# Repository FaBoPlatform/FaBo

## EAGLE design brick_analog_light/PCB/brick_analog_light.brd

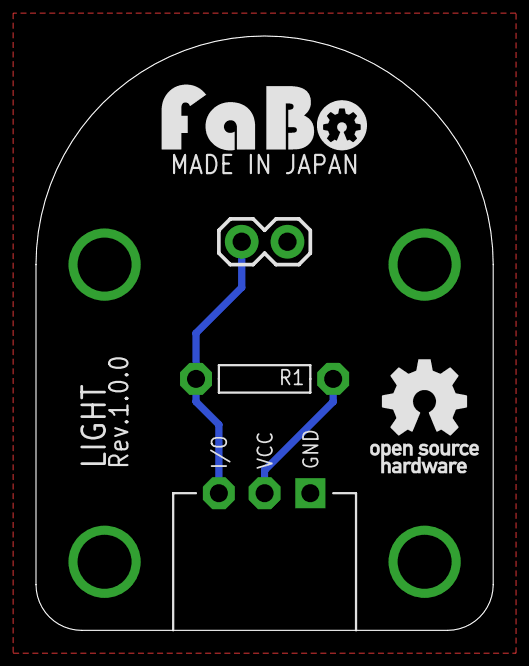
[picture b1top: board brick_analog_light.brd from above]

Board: 2 copper layers, 25.4 x 33.0 mm, 5 parts (0 on the bottom side), 3 nets.

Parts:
J1: FABO_BRICK_3PIN
R1: 10k; RES-AXL-REGULAR
U1: 1X02
U$2: LOGO_OSHW_T_M
U$3: LOGO_FABO_M

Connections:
GND: J1.GND, U1.2
unnamed: J1.VCC, R1.P$1
unnamed: J1.IN/OUT, R1.P$2, U1.1

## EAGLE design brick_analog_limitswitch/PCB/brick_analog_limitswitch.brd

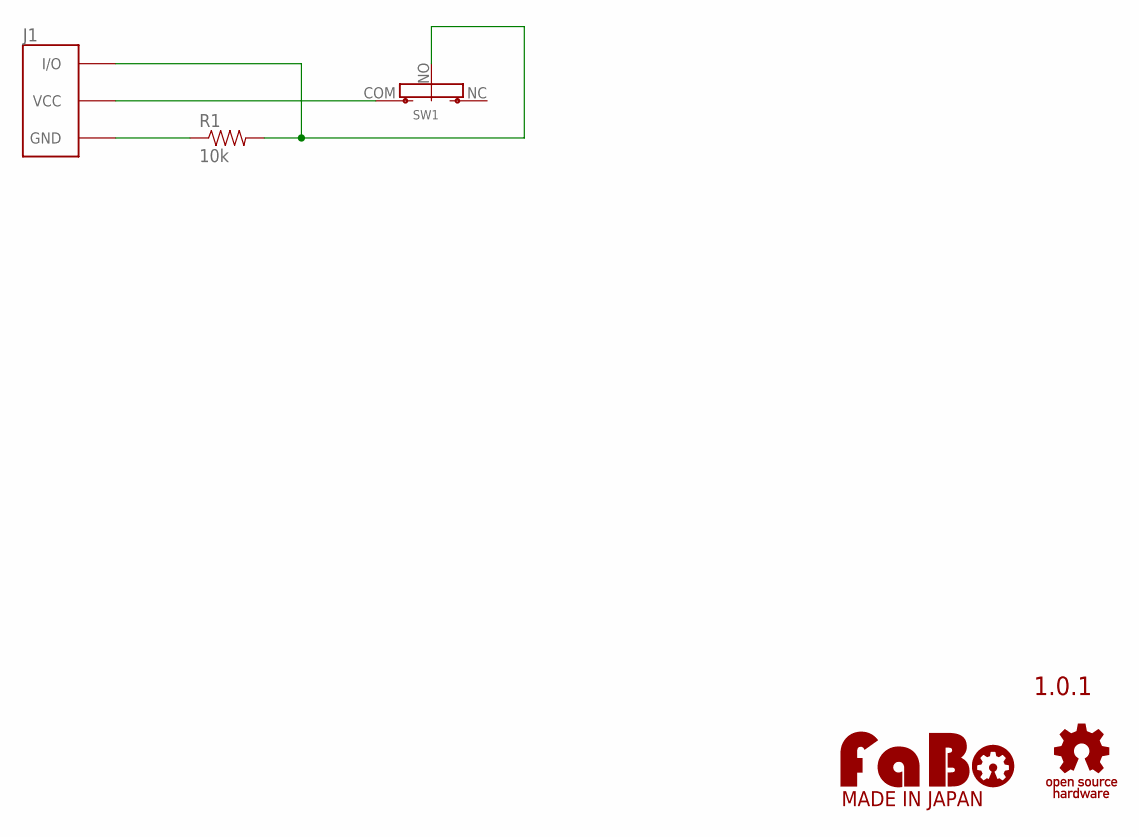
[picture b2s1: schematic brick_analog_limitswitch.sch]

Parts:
J1: FABO_BRICK_3PIN
R1: 10k; RES-AXL-REGULAR
SW1: LIMIT-SWITCH
U$2: LOGO_OSHW-T_M; LOGO_OSHW_T_M
U$4: LOGO_FABO-M; LOGO_FABO_M

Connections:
GND: J1.GND, R1.P$1 (1)
unnamed: J1.VCC, SW1.COM (VCC)
unnamed: J1.IN/OUT (I/O), R1.P$2 (2), SW1.NO

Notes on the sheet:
1.0.1

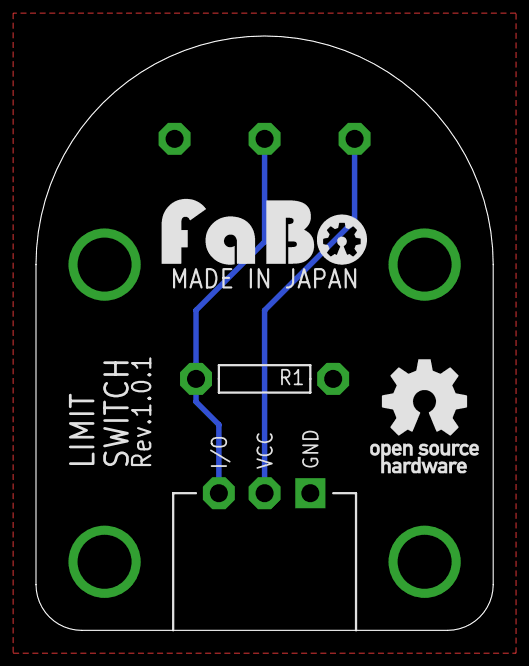
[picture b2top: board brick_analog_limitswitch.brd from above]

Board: 2 copper layers, 25.4 x 33.0 mm, 5 parts (0 on the bottom side), 3 nets.

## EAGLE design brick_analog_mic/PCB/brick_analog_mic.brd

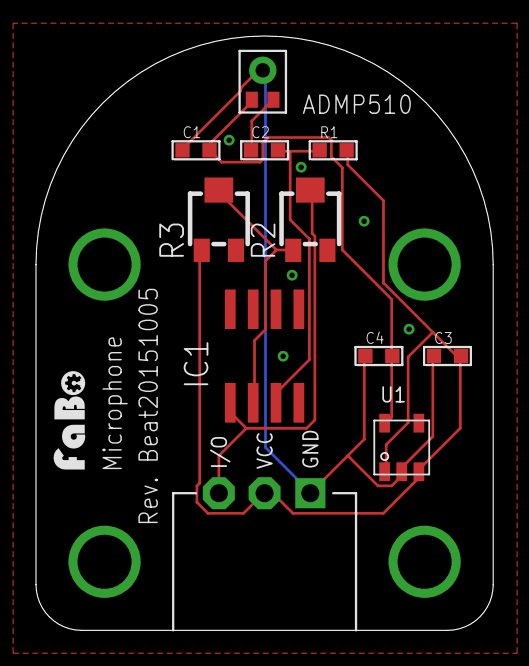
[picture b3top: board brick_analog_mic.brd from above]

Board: 2 copper layers, 25.4 x 33.0 mm, 12 parts (0 on the bottom side), 7 nets.

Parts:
C1: 0.1uF; 0603
C2, C3, C4: 1uf; 0603
IC1: ADA4075; SO8
J1: FABO_BRICK_3PIN
R1: 10k; 0603
R2, R3: RTRIM3202
U1: SOT_23_5
U$1: ANALOGDEVICES-ADMP510
U$2: LOGO_FABO_S

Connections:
3V3: C1.2, C4.2, U1.5, U$1.1
5V: C3.2, J1.VCC, R1.2, R3.1, U1.1, U1.3
GND: C1.1, C3.1, C4.1, J1.GND, U1.2, U$1.3
unnamed: C2.1, U$1.2
unnamed: C2.2, IC1.3, R1.1
unnamed: IC1.1, J1.IN/OUT, R2.2
unnamed: IC1.2, R2.1, R3.2

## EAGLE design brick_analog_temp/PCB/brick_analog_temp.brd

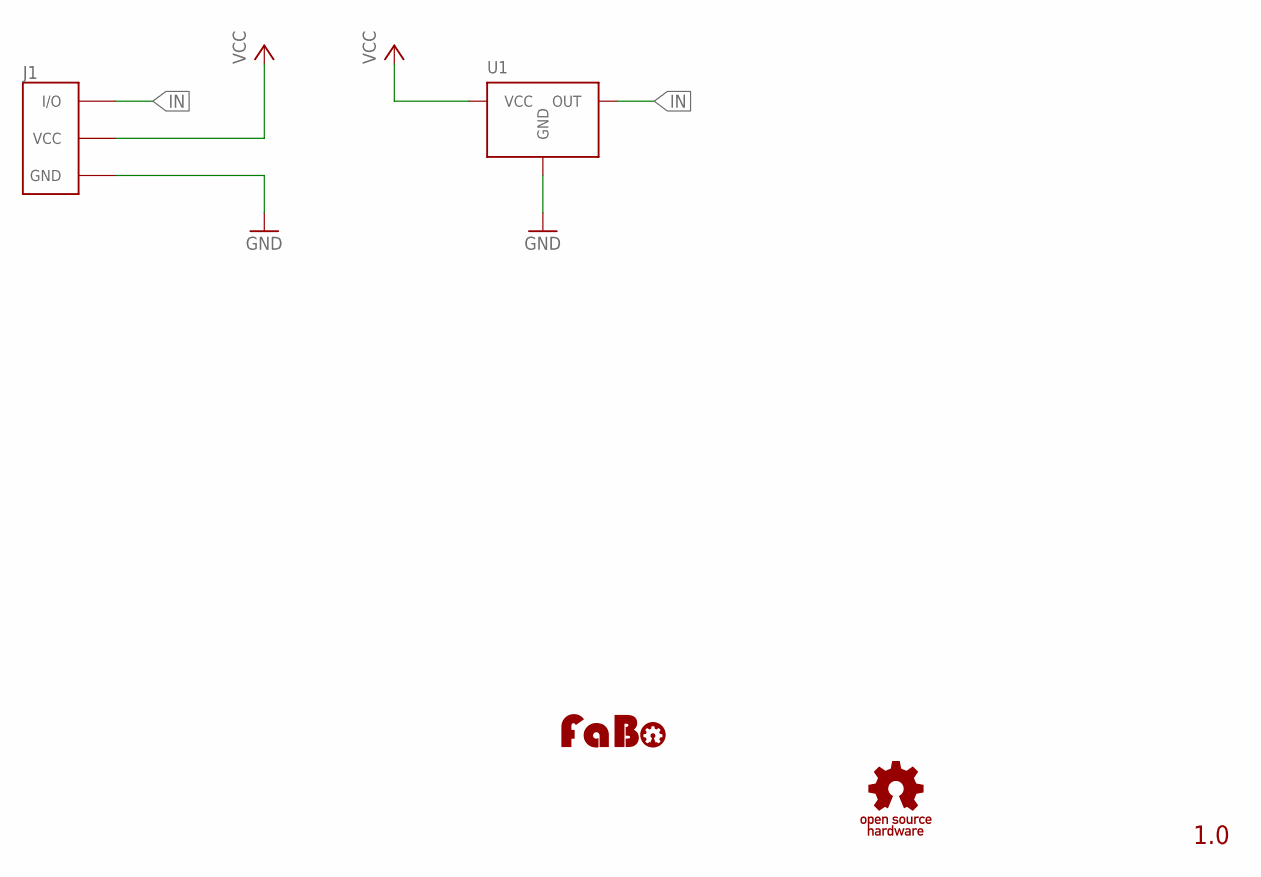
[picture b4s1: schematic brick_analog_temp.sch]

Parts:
J1: BRICK_3PIN_NORMAL; BRICK_3PIN
U1: SENSOR-LM60-TO92; SENSOR-LM60-TO-92
U$2: LOGO_OSHW_T-M; LOGO_OSHW_T_M
U$3: LOGO_FABO-M; LOGO_FABO_M

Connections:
GND: J1.GND, U1.GND
IN: J1.IN/OUT (I/O), U1.OUT
VCC: J1.VCC, U1.VCC

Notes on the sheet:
1.0

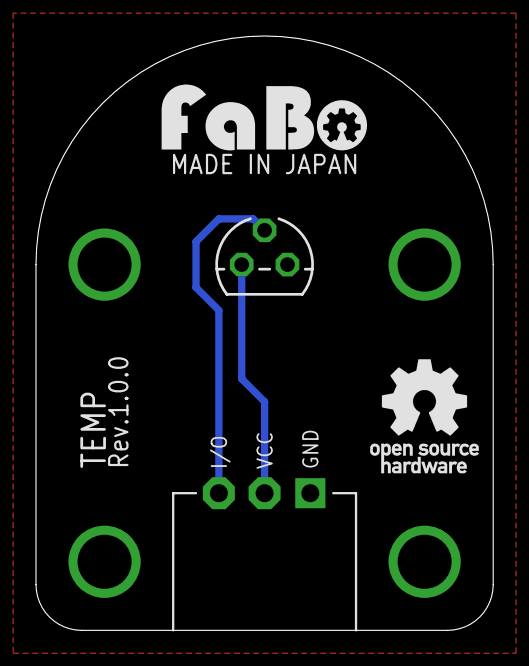
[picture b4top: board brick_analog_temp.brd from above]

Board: 2 copper layers, 25.4 x 33.0 mm, 4 parts (0 on the bottom side), 3 nets.

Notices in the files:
parts and their libraries:
SparkFun: Licensing: CC v3.0 Share-Alike You are welcome to use this library for commercial purposes.
FaBo-Template: Released under the Creative Commons Attribution-ShareAlike 4.0 License
https://creativecommons.org/licenses/by-sa/4.0
FaBo-etc: Released under the Creative Commons
